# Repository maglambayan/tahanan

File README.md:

# Tahanan Hub

A Home Assistant hub built on the Raspberry Pi Compute Module 5: NVMe storage, Gigabit Ethernet with
802.3bt PoE, USB-C Power Delivery, Wi-Fi and Bluetooth, Zigbee, Thread and Matter, a Z-Wave module
socket, and a microphone, codec and speaker output for voice.

**Revision A is a design package, not a finished product.** The schematic is complete and passes ERC.
The board is placed but not routed, so there are no fabrication files yet. No hardware has been built
and nothing has been validated. Read [docs/status.md](docs/status.md) first.

Since the first commit the open component values and part numbers were checked, the BOM was priced
against DigiKey, and the firmware and Home Assistant OS build files were completed and corrected.
Routing, fabrication files, builds and all testing are still open.

## Layout of this repository

| Path | Contents |
|---|---|
| `docs/` | SoC evaluation, architecture, power and thermal, PCB guide, mechanical, software and recovery, validation plan, status |
| `hardware/` | KiCad 10 project: schematic sheets, board, project library, rules |
| `hardware/gen/` | Generator. `design.py` is the circuit. The KiCad files are built from it |
| `manufacturing/bom/` | Board BOM and system BOM as CSV |
| `mechanical/` | Parametric enclosure script and exported STEP, STL, 3MF |
| `software/` | Bootloader config, `config.txt` block, device tree overlay, Home Assistant OS build recipe |
| `firmware/` | USB-PD controller settings and programming script, radio firmware manifests |

## Building

Needs KiCad 10 and Python 3. From `hardware/`:

```
make sch erc     # schematic, netlist comparison, electrical rule check
make pcb drc     # placed board, design rule check
make docs        # schematic PDF, placement drawing, board STEP, BOM
make fab         # fabrication outputs. Refuses until the board is routed and DRC-clean
```

Enclosure, with CadQuery installed: `python mechanical/enclosure.py`.

The schematic sheets and the board are editable in KiCad. Edits made there are overwritten by the
generator, so either change `design.py` or stop using the generator once manual layout begins.

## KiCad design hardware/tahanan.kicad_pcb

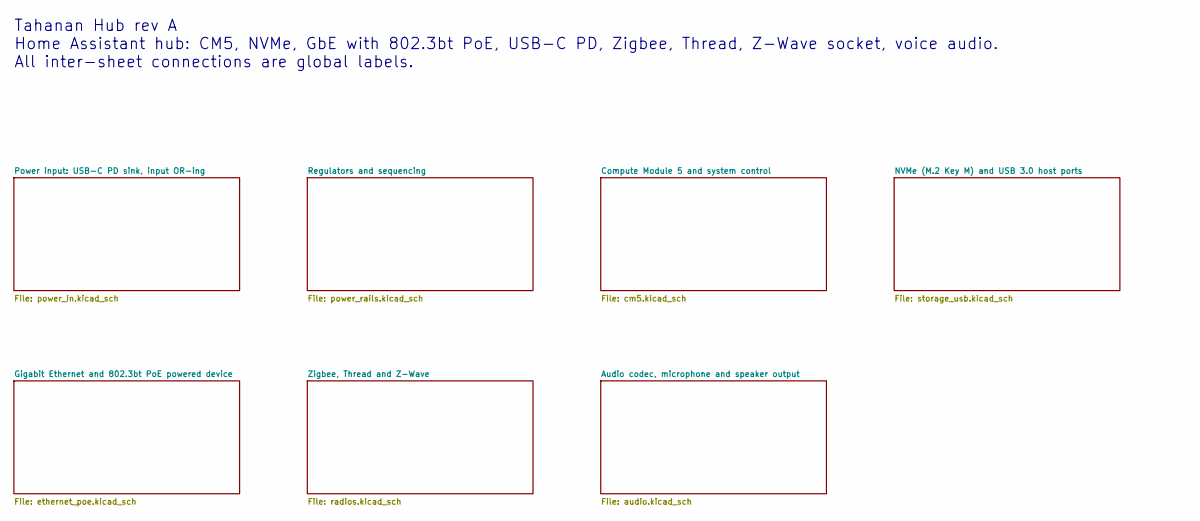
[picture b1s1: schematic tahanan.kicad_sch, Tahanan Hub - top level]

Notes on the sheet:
Tahanan Hub rev A Home Assistant hub: CM5, NVMe, GbE with 802.3bt PoE, USB-C PD, Zigbee, Thread, Z-Wave socket, voice audio. All inter-sheet connections are global labels.

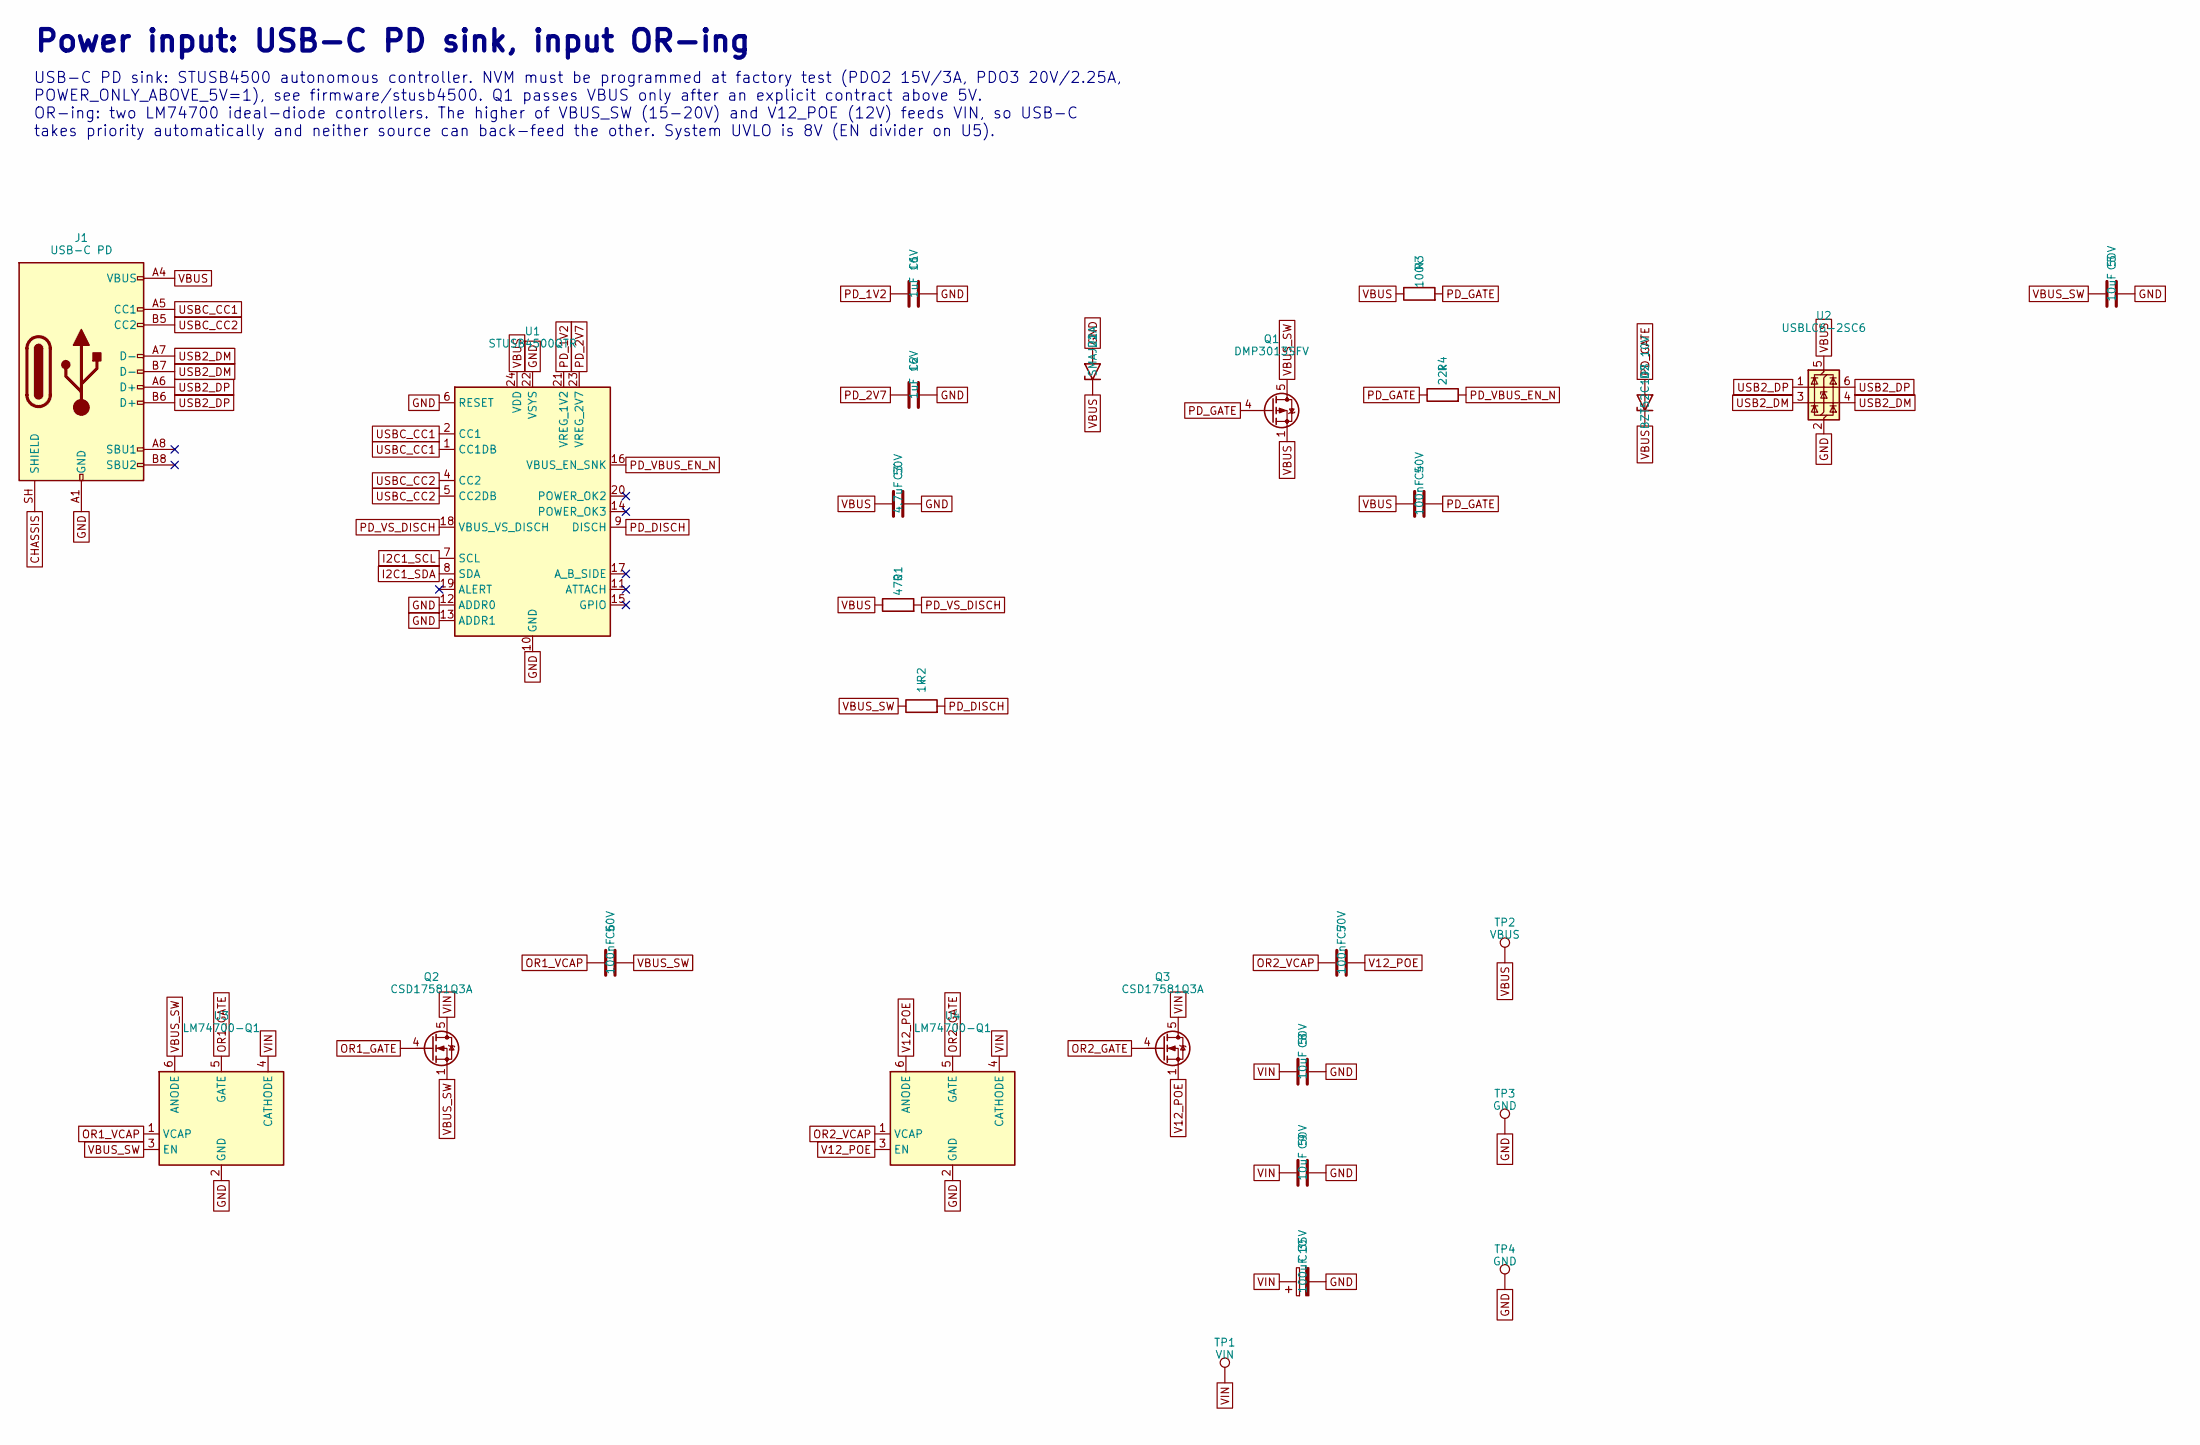
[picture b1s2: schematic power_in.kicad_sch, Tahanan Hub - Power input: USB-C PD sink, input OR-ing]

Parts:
C1, C2: 1uF 16V; C_0402_1005Metric; MPN CL05A105KO5NNNC
C3: 4.7uF 50V; C_0805_2012Metric; MPN CL21A475KBQNNNE
C4, C6, C7: 100nF 50V; C_0603_1608Metric; MPN CL10B104KB8NNNC
C5, C8, C9: 10uF 50V; C_1210_3225Metric; MPN CL32B106KBJNNNE
C10: 100uF 35V; CP_Elec_6.3x7.7; MPN EEE-FT1V101AP
D1: SMAJ22A; D_SMA; MPN SMAJ22A
D2: BZT52C10S 10V; D_SOD-323; MPN BZT52C10S-7-F
J1: USB-C PD; USB_C_Receptacle_GCT_USB4105-xx-A_16P_TopMnt_Horizontal; MPN USB4105-GF-A
Q1: DMP3013SFV; Diodes_PowerDI3333-8; MPN DMP3013SFV-7
Q2, Q3: CSD17581Q3A; VSON-8_3.3x3.3mm_P0.65mm_NexFET; MPN CSD17581Q3A
R1: 470; R_0402_1005Metric; MPN RC0402FR-07470RL
R2: 1k; R_0603_1608Metric; MPN RC0603FR-071kL
R3: 100k; R_0402_1005Metric; MPN RC0402FR-07100kL
R4: 22k; R_0402_1005Metric; MPN RC0402FR-0722kL
TP1: VIN; TestPoint_Pad_D1.5mm
TP2: VBUS; TestPoint_Pad_D1.5mm
TP3, TP4: GND; TestPoint_Pad_D1.5mm
U1: STUSB4500QTR; QFN-24-1EP_4x4mm_P0.5mm_EP2.7x2.7mm; MPN STUSB4500QTR
U2: USBLC6-2SC6; SOT-23-6; MPN USBLC6-2SC6
U3, U4: LM74700-Q1; SOT-23-6; MPN LM74700QDBVRQ1

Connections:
CHASSIS: J1.SH (SHIELD); also elsewhere on the board
GND: C1.2, C2.2, C3.2, C5.2, C8.2, C9.2, C10.2, D1.2 (A2), J1.A1 (GND), J1.A12 (GND), J1.B1 (GND), J1.B12 (GND), TP3.1, TP4.1, U1.6 (RESET), U1.10 (GND), U1.12 (ADDR0), U1.13 (ADDR1), U1.22 (VSYS), U1.25 (GND), U2.2 (GND), U3.2 (GND), U4.2 (GND); also elsewhere on the board
I2C1_SCL: U1.7 (SCL); also elsewhere on the board
I2C1_SDA: U1.8 (SDA); also elsewhere on the board
OR1_GATE: Q2.4 (G), U3.5 (GATE)
OR1_VCAP: C6.1, U3.1 (VCAP)
OR2_GATE: Q3.4 (G), U4.5 (GATE)
OR2_VCAP: C7.1, U4.1 (VCAP)
PD_1V2: C1.1, U1.21 (VREG_1V2)
PD_2V7: C2.1, U1.23 (VREG_2V7)
PD_DISCH: R2.2, U1.9 (DISCH)
PD_GATE: C4.2, D2.2 (A), Q1.4 (G), R3.2, R4.1
PD_VBUS_EN_N: R4.2, U1.16 (VBUS_EN_SNK)
PD_VS_DISCH: R1.2, U1.18 (VBUS_VS_DISCH)
USB2_DM: J1.A7 (D-), J1.B7 (D-), U2.3 (I/O2), U2.4 (I/O2); also elsewhere on the board
USB2_DP: J1.A6 (D+), J1.B6 (D+), U2.1 (I/O1), U2.6 (I/O1); also elsewhere on the board
USBC_CC1: J1.A5 (CC1), U1.1 (CC1DB), U1.2 (CC1)
USBC_CC2: J1.B5 (CC2), U1.4 (CC2), U1.5 (CC2DB)
V12_POE: C7.2, Q3.1 (S), Q3.2 (S), Q3.3 (S), U4.3 (EN), U4.6 (ANODE); also elsewhere on the board
VBUS: C3.1, C4.1, D1.1 (A1), D2.1 (K), J1.A4 (VBUS), J1.A9 (VBUS), J1.B4 (VBUS), J1.B9 (VBUS), Q1.1 (S), Q1.2 (S), Q1.3 (S), R1.1, R3.1, TP2.1, U1.24 (VDD), U2.5 (VBUS)
VBUS_SW: C5.1, C6.2, Q1.5 (D), Q2.1 (S), Q2.2 (S), Q2.3 (S), R2.1, U3.3 (EN), U3.6 (ANODE)
VIN: C8.1, C9.1, C10.1, Q2.5 (D), Q3.5 (D), TP1.1, U3.4 (CATHODE), U4.4 (CATHODE); also elsewhere on the board

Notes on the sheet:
Power input: USB-C PD sink, input OR-ing
USB-C PD sink: STUSB4500 autonomous controller. NVM must be programmed at factory test (PDO2 15V/3A, PDO3 20V/2.25A, POWER_ONLY_ABOVE_5V=1), see firmware/stusb4500. Q1 passes VBUS only after an explicit contract above 5V. OR-ing: two LM74700 ideal-diode controllers. The higher of VBUS_SW (15-20V) a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

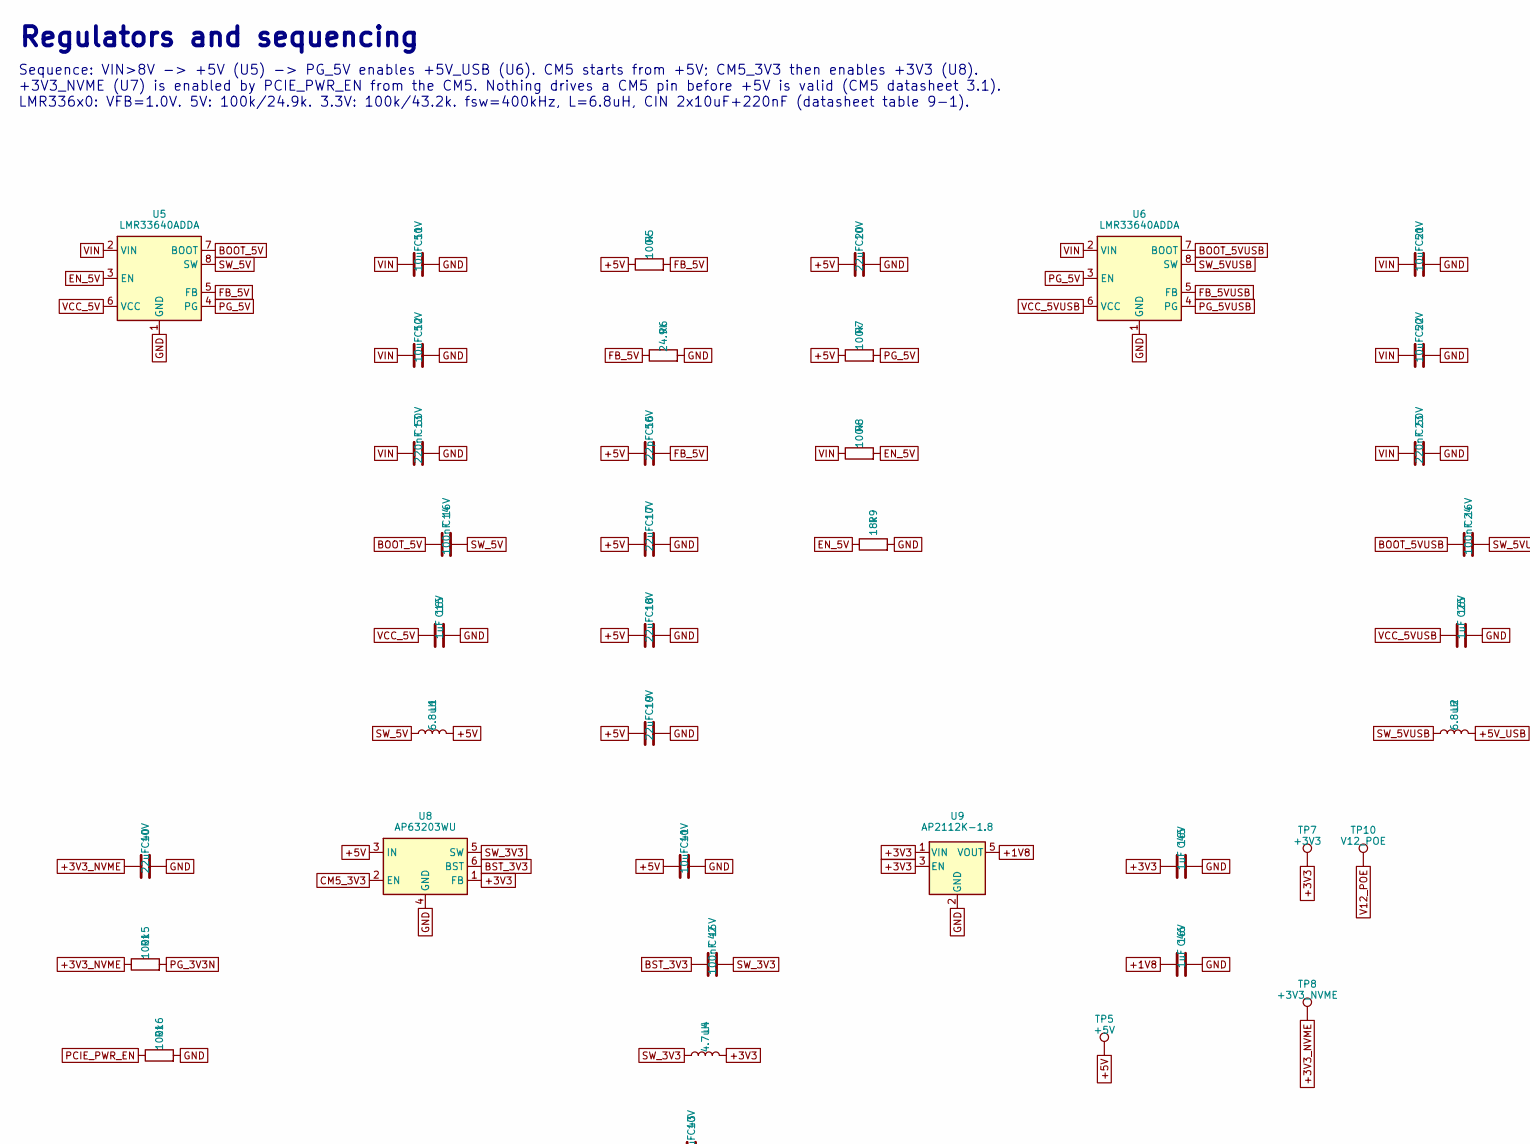
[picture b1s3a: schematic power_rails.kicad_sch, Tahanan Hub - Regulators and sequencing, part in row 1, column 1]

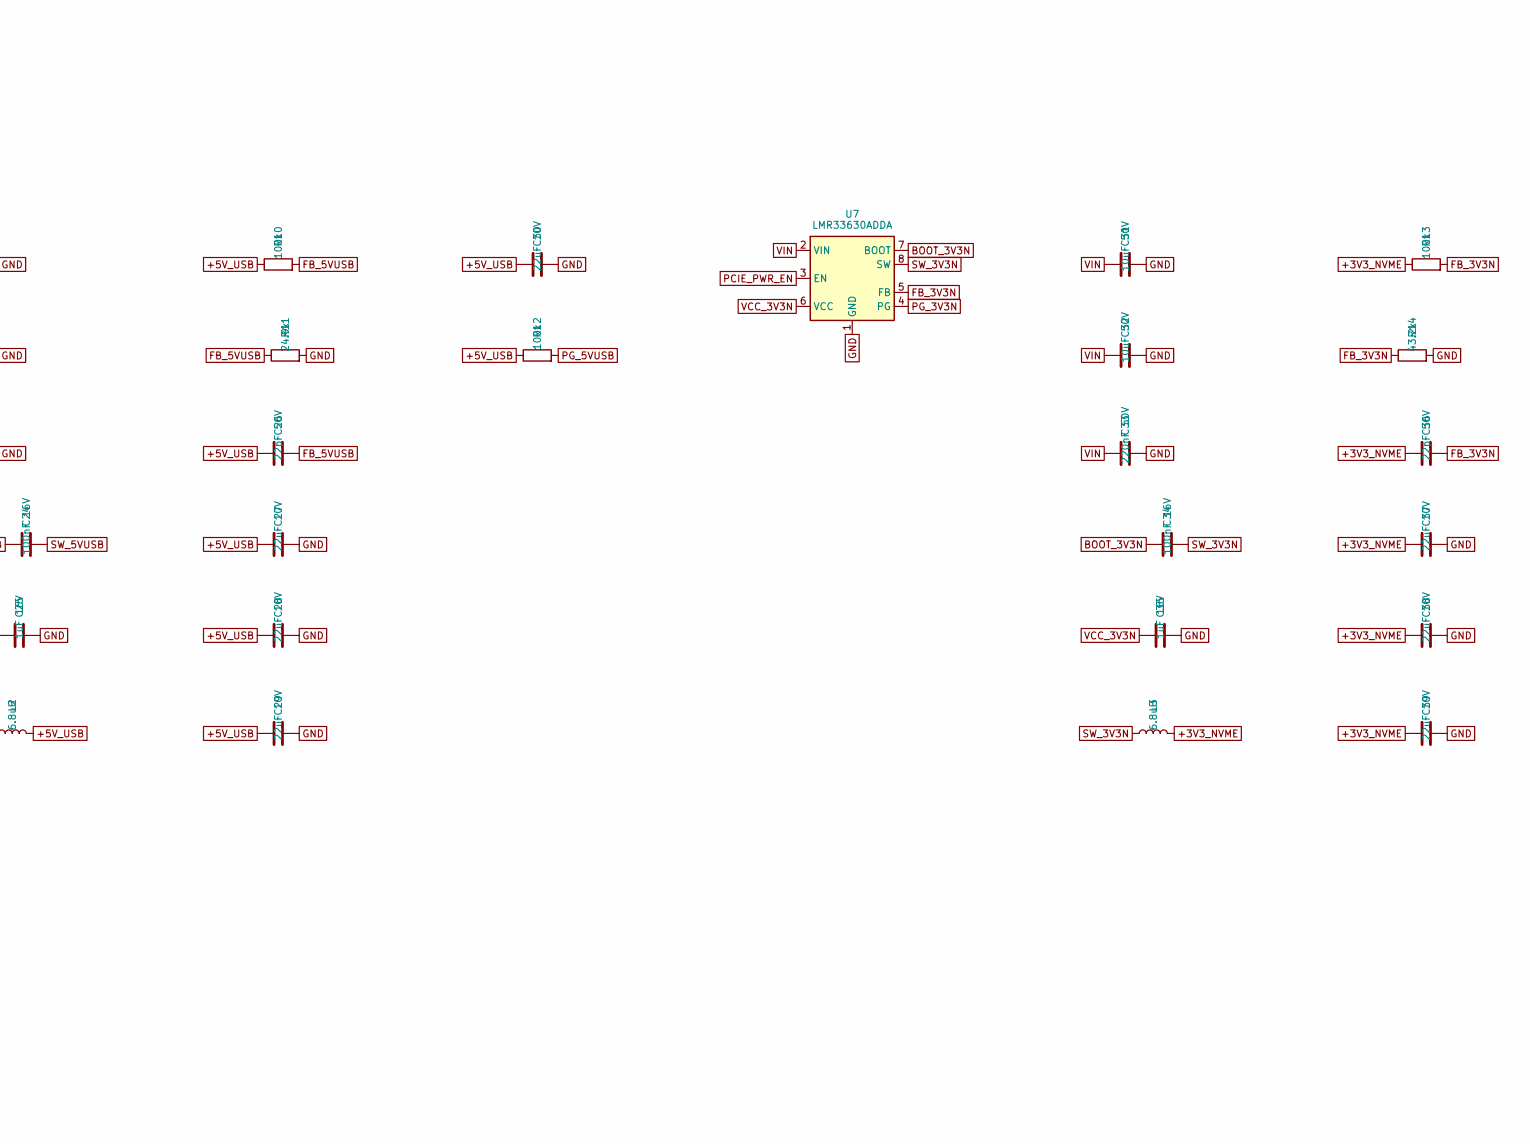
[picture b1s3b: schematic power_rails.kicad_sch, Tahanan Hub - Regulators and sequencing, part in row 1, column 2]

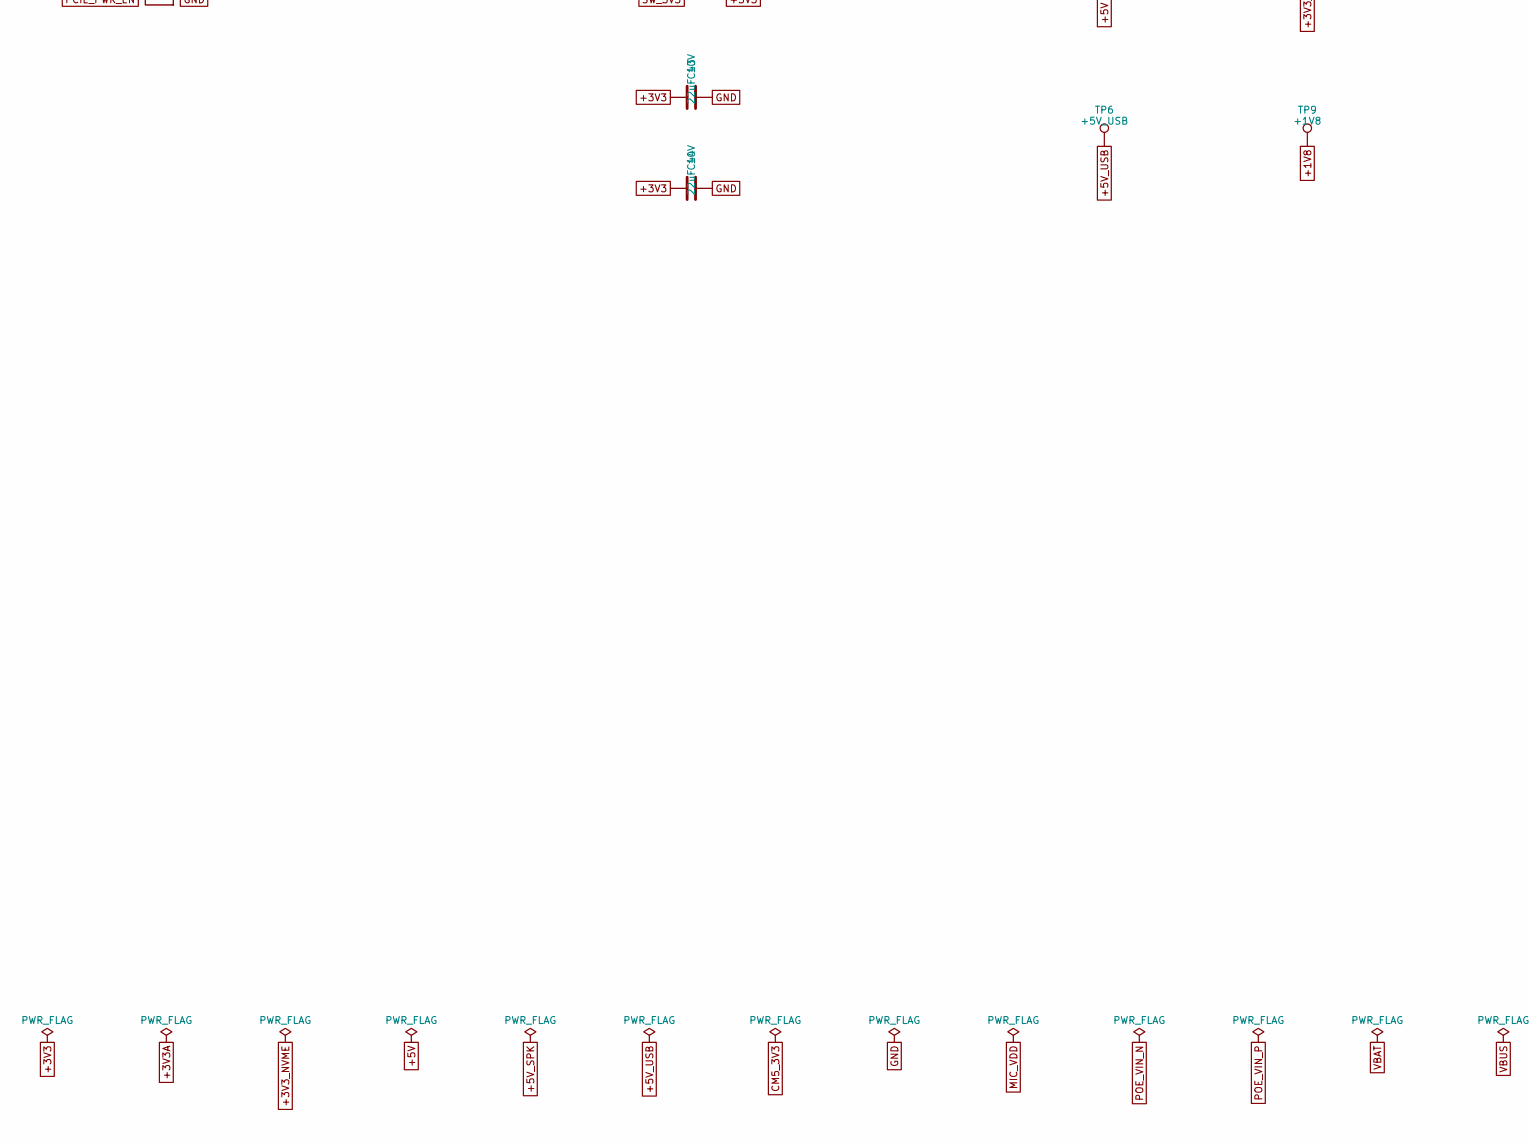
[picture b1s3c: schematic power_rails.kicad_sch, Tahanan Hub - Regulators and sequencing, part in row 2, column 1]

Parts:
C11, C12, C21, C22, C31, C32: 10uF 50V; C_1210_3225Metric; MPN CL32B106KBJNNNE
C13, C23, C33: 220nF 50V; C_0603_1608Metric; MPN CL10B224KB8NNNC
C14, C24, C34, C42: 100nF 16V; C_0402_1005Metric; MPN CL05B104KO5NNNC
C15, C25, C35, C45, C46: 1uF 16V; C_0402_1005Metric; MPN CL05A105KO5NNNC
C16, C26, C36: 22pF 50V; C_0402_1005Metric; MPN CL05C220JB5NNNC
C17, C18, C19, C20, C27, C28, C29, C30, C37, C38, C39, C40, C43, C44: 22uF 10V; C_0805_2012Metric; MPN CL21A226MPQNNNE
C41: 10uF 10V; C_0603_1608Metric; MPN CL10A106KP8NNNC
L1, L2, L3: 6.8uH; L_Bourns_SRP1038C_10.0x10.0mm; MPN SRP1038CC-6R8M
L4: 4.7uH; L_Bourns-SRN4018; MPN SRN4018-4R7M
R5, R7, R8, R10, R12, R13, R15, R16: 100k; R_0402_1005Metric; MPN RC0402FR-07100kL
R6, R11: 24.9k; R_0402_1005Metric; MPN RC0402FR-0724k9L
R9: 18k; R_0402_1005Metric; MPN RC0402FR-0718kL
R14: 43.2k; R_0402_1005Metric; MPN RC0402FR-0743k2L
TP5: +5V; TestPoint_Pad_D1.5mm
TP6: +5V_USB; TestPoint_Pad_D1.5mm
TP7: +3V3; TestPoint_Pad_D1.5mm
TP8: +3V3_NVME; TestPoint_Pad_D1.5mm
TP9: +1V8; TestPoint_Pad_D1.5mm
TP10: V12_POE; TestPoint_Pad_D1.5mm
U5, U6: LMR33640ADDA; Texas_HSOP-8-1EP_3.9x4.9mm_P1.27mm_ThermalVias; MPN LMR33640ADDAR
U7: LMR33630ADDA; Texas_HSOP-8-1EP_3.9x4.9mm_P1.27mm_ThermalVias; MPN LMR33630ADDAR
U8: AP63203WU; TSOT-23-6; MPN AP63203WU-7
U9: AP2112K-1.8; SOT-23-5; MPN AP2112K-1.8TRG1

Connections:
+1V8: C46.1, TP9.1, U9.5 (VOUT); also elsewhere on the board
+3V3: C43.1, C44.1, C45.1, L4.2, TP7.1, U8.1 (FB), U9.1 (VIN), U9.3 (EN); also elsewhere on the board
+3V3_NVME: C36.1, C37.1, C38.1, C39.1, C40.1, L3.2, R13.1, R15.1, TP8.1; also elsewhere on the board
+5V: C16.1, C17.1, C18.1, C19.1, C20.1, C41.1, L1.2, R5.1, R7.1, TP5.1, U8.3 (IN); also elsewhere on the board
+5V_USB: C26.1, C27.1, C28.1, C29.1, C30.1, L2.2, R10.1, R12.1, TP6.1; also elsewhere on the board
BOOT_3V3N: C34.1, U7.7 (BOOT)
BOOT_5V: C14.1, U5.7 (BOOT)
BOOT_5VUSB: C24.1, U6.7 (BOOT)
BST_3V3: C42.1, U8.6 (BST)
CM5_3V3: U8.2 (EN); also elsewhere on the board
EN_5V: R8.2, R9.1, U5.3 (EN)
FB_3V3N: C36.2, R13.2, R14.1, U7.5 (FB)
FB_5V: C16.2, R5.2, R6.1, U5.5 (FB)
FB_5VUSB: C26.2, R10.2, R11.1, U6.5 (FB)
GND: C11.2, C12.2, C13.2, C15.2, C17.2, C18.2, C19.2, C20.2, C21.2, C22.2, C23.2, C25.2, C27.2, C28.2, C29.2, C30.2, C31.2, C32.2, C33.2, C35.2, C37.2, C38.2, C39.2, C40.2, C41.2, C43.2, C44.2, C45.2, C46.2, R6.2, R9.2, R11.2, R14.2, R16.2, U5.1 (GND), U5.9 (GND), U6.1 (GND), U6.9 (GND), U7.1 (GND), U7.9 (GND), U8.4 (GND), U9.2 (GND); also elsewhere on the board
PCIE_PWR_EN: R16.1, U7.3 (EN); also elsewhere on the board
PG_3V3N: R15.2, U7.4 (PG)
PG_5V: R7.2, U5.4 (PG), U6.3 (EN)
PG_5VUSB: R12.2, U6.4 (PG)
SW_3V3: C42.2, L4.1, U8.5 (SW)
SW_3V3N: C34.2, L3.1, U7.8 (SW)
SW_5V: C14.2, L1.1, U5.8 (SW)
SW_5VUSB: C24.2, L2.1, U6.8 (SW)
V12_POE: TP10.1; also elsewhere on the board
VCC_3V3N: C35.1, U7.6 (VCC)
VCC_5V: C15.1, U5.6 (VCC)
VCC_5VUSB: C25.1, U6.6 (VCC)
VIN: C11.1, C12.1, C13.1, C21.1, C22.1, C23.1, C31.1, C32.1, C33.1, R8.1, U5.2 (VIN), U6.2 (VIN), U7.2 (VIN); also elsewhere on the board

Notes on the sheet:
Regulators and sequencing
Sequence: VIN>8V -> +5V (U5) -> PG_5V enables +5V_USB (U6). CM5 starts from +5V; CM5_3V3 then enables +3V3 (U8). +3V3_NVME (U7) is enabled by PCIE_PWR_EN from the CM5. Nothing drives a CM5 pin before +5V is valid (CM5 datasheet 3.1). LMR336x0: VFB=1.0V. 5V: 100k/24.9k. 3.3V: 100k/43.2k. fsw=400kHz,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

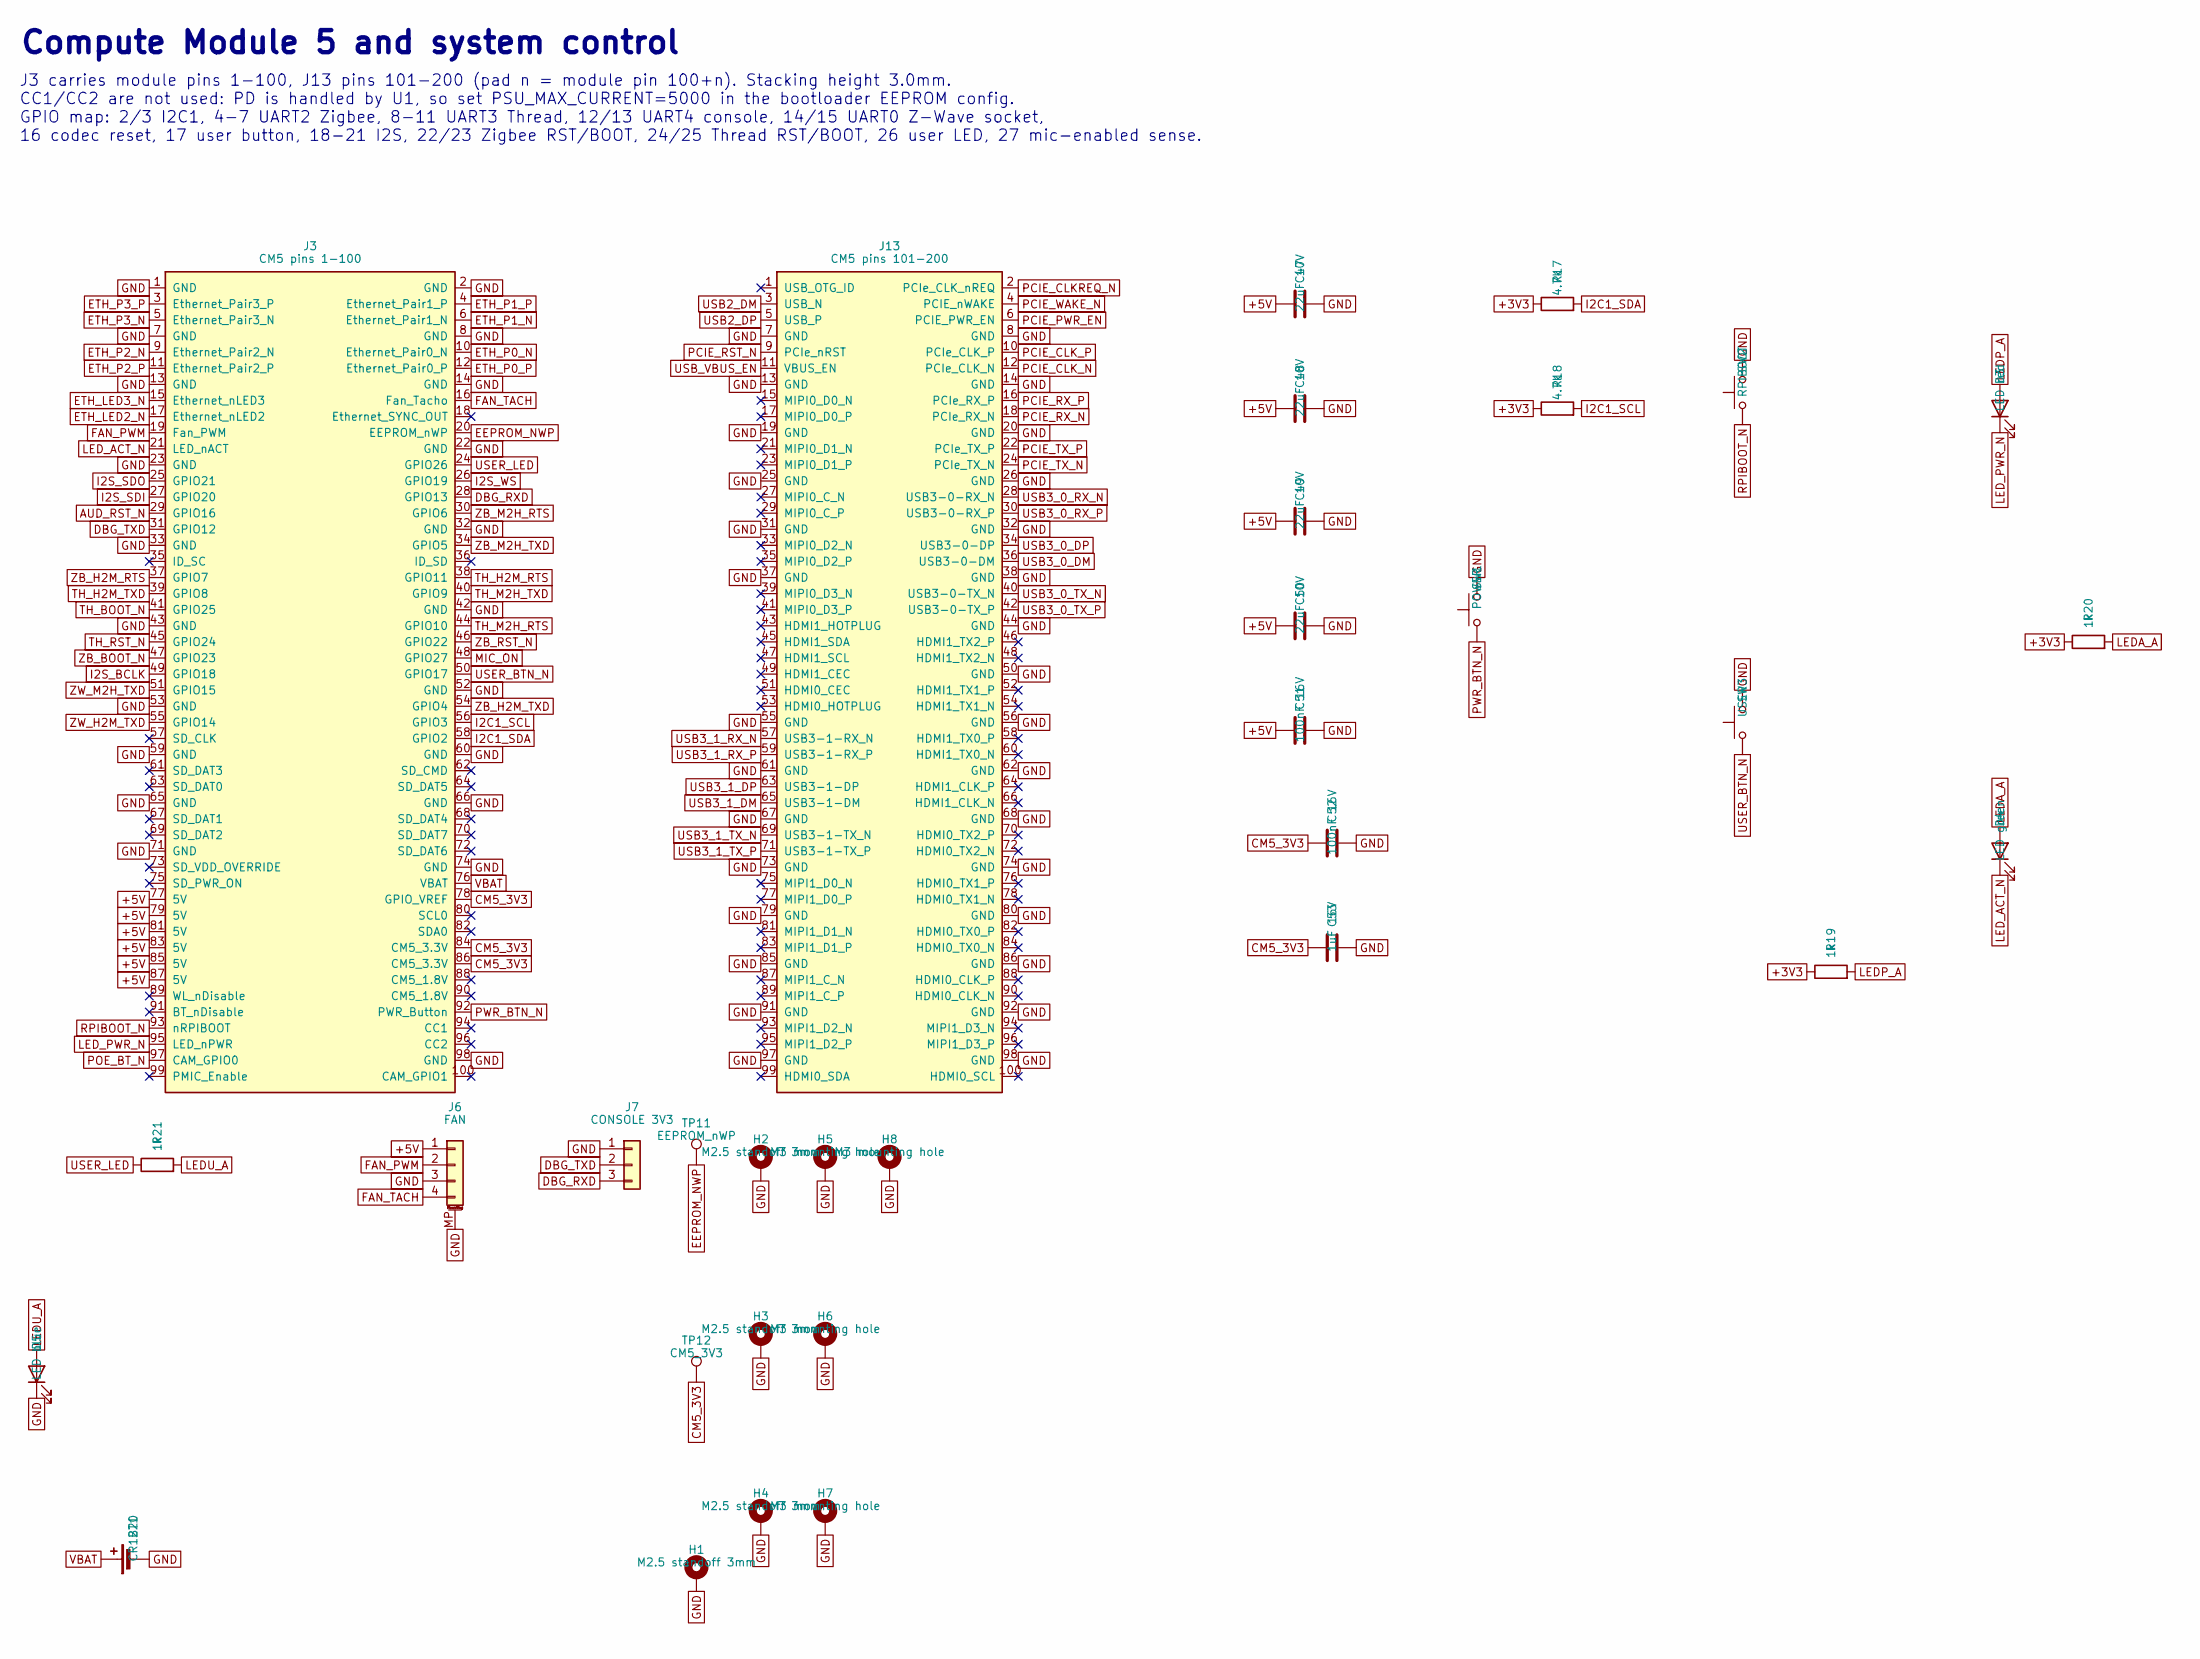
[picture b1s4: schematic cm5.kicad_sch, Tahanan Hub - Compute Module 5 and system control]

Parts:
BT1: CR1220; BatteryHolder_Keystone_3000_1x12mm; MPN 3000
C47, C48, C49, C50: 22uF 10V; C_0805_2012Metric; MPN CL21A226MPQNNNE
C51, C52: 100nF 16V; C_0402_1005Metric; MPN CL05B104KO5NNNC
C53: 1uF 16V; C_0402_1005Metric; MPN CL05A105KO5NNNC
D3: LED red; LED_0603_1608Metric; MPN 150060RS75000
D4: LED green; LED_0603_1608Metric; MPN 150060GS75000
D5: LED blue; LED_0603_1608Metric; MPN 150060BS75000
H1, H2, H3, H4: M2.5 standoff 3mm; Mounting_Wuerth_WA-SMSI-M2.5_H3mm_9774030151; MPN 9774030151R
H5, H6, H7, H8: M3 mounting hole; MountingHole_3.2mm_M3_Pad_Via
J3: CM5 pins 1-100; Hirose_DF40HC(3.0)-100DS-0.4V_2x50_P0.4mm; MPN DF40HC(3.0)-100DS-0.4V(51)
J6: FAN; JST_SH_SM04B-SRSS-TB_1x04-1MP_P1.00mm_Horizontal; MPN SM04B-SRSS-TB
J7: CONSOLE 3V3; PinHeader_1x03_P2.54mm_Vertical; MPN 61300311121
J13: CM5 pins 101-200; Hirose_DF40HC(3.0)-100DS-0.4V_2x50_P0.4mm; MPN DF40HC(3.0)-100DS-0.4V(51)
R17, R18: 4.7k; R_0402_1005Metric; MPN RC0402FR-074k7L
R19, R20, R21: 1k; R_0402_1005Metric; MPN RC0402FR-071kL
SW1: POWER; SW_Tactile_SPST_NO_Straight_CK_PTS636Sx25SMTRLFS; MPN PTS636SM25FSMTRLFS
SW2: RPIBOOT; SW_Tactile_SPST_NO_Straight_CK_PTS636Sx25SMTRLFS; MPN PTS636SM25FSMTRLFS
SW3: USER; SW_Tactile_SPST_NO_Straight_CK_PTS636Sx25SMTRLFS; MPN PTS636SM25FSMTRLFS
TP11: EEPROM_nWP; TestPoint_Pad_D1.5mm
TP12: CM5_3V3; TestPoint_Pad_D1.5mm

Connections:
+3V3: R17.1, R18.1, R19.1, R20.1; also elsewhere on the board
+5V: C47.1, C48.1, C49.1, C50.1, C51.1, J3.77 (5V), J3.79 (5V), J3.81 (5V), J3.83 (5V), J3.85 (5V), J3.87 (5V), J6.1; also elsewhere on the board
AUD_RST_N: J3.29 (GPIO16); also elsewhere on the board
CM5_3V3: C52.1, C53.1, J3.78 (GPIO_VREF), J3.84 (CM5_3.3V), J3.86 (CM5_3.3V), TP12.1; also elsewhere on the board
DBG_RXD: J3.28 (GPIO13), J7.3
DBG_TXD: J3.31 (GPIO12), J7.2
EEPROM_NWP: J3.20 (EEPROM_nWP), TP11.1
ETH_LED2_N: J3.17 (Ethernet_nLED2); also elsewhere on the board
ETH_LED3_N: J3.15 (Ethernet_nLED3); also elsewhere on the board
ETH_P0_N: J3.10 (Ethernet_Pair0_N); also elsewhere on the board
ETH_P0_P: J3.12 (Ethernet_Pair0_P); also elsewhere on the board
ETH_P1_N: J3.6 (Ethernet_Pair1_N); also elsewhere on the board
ETH_P1_P: J3.4 (Ethernet_Pair1_P); also elsewhere on the board
ETH_P2_N: J3.9 (Ethernet_Pair2_N); also elsewhere on the board
ETH_P2_P: J3.11 (Ethernet_Pair2_P); also elsewhere on the board
ETH_P3_N: J3.5 (Ethernet_Pair3_N); also elsewhere on the board
ETH_P3_P: J3.3 (Ethernet_Pair3_P); also elsewhere on the board
FAN_PWM: J3.19 (Fan_PWM), J6.2
FAN_TACH: J3.16 (Fan_Tacho), J6.4
GND: BT1.2 (-), C47.2, C48.2, C49.2, C50.2, C51.2, C52.2, C53.2, D5.1 (K), H1.1, H2.1, H3.1, H4.1, H5.1, H6.1, H7.1, H8.1, J3.1 (GND), J3.2 (GND), J3.7 (GND), J3.8 (GND), J3.13 (GND), J3.14 (GND), J3.22 (GND), J3.23 (GND), J3.32 (GND), J3.33 (GND), J3.42 (GND), J3.43 (GND), J3.52 (GND), J3.53 (GND), J3.59 (GND), J3.60 (GND), J3.65 (GND), J3.66 (GND), J3.71 (GND), J3.74 (GND), J3.98 (GND), J6.3, J6.MP (MountPin), J7.1, J13.7 (GND), J13.8 (GND), J13.13 (GND), J13.14 (GND), J13.19 (GND), J13.20 (GND), J13.25 (GND), J13.26 (GND), J13.31 (GND), J13.32 (GND), J13.37 (GND), J13.38 (GND), J13.44 (GND), J13.50 (GND), J13.55 (GND), J13.56 (GND), J13.61 (GND), J13.62 (GND), J13.67 (GND), J13.68 (GND), J13.73 (GND), J13.74 (GND), J13.79 (GND), J13.80 (GND), J13.85 (GND), J13.86 (GND), J13.91 (GND), J13.92 (GND), J13.97 (GND), J13.98 (GND), SW1.2, SW2.2, SW3.2; also elsewhere on the board
I2C1_SCL: J3.56 (GPIO3), R18.2; also elsewhere on the board
I2C1_SDA: J3.58 (GPIO2), R17.2; also elsewhere on the board
I2S_BCLK: J3.49 (GPIO18); also elsewhere on the board
I2S_SDI: J3.27 (GPIO20); also elsewhere on the board
I2S_SDO: J3.25 (GPIO21); also elsewhere on the board
I2S_WS: J3.26 (GPIO19); also elsewhere on the board
LEDA_A: D4.2 (A), R20.2
LEDP_A: D3.2 (A), R19.2
LEDU_A: D5.2 (A), R21.2
LED_ACT_N: D4.1 (K), J3.21 (LED_nACT)
LED_PWR_N: D3.1 (K), J3.95 (LED_nPWR)
MIC_ON: J3.48 (GPIO27); also elsewhere on the board
PCIE_CLKREQ_N: J13.2 (PCIe_CLK_nREQ); also elsewhere on the board
PCIE_CLK_N: J13.12 (PCIe_CLK_N); also elsewhere on the board
PCIE_CLK_P: J13.10 (PCIe_CLK_P); also elsewhere on the board
PCIE_PWR_EN: J13.6 (PCIE_PWR_EN); also elsewhere on the board
PCIE_RST_N: J13.9 (PCIe_nRST); also elsewhere on the board
PCIE_RX_N: J13.18 (PCIe_RX_N); also elsewhere on the board
PCIE_RX_P: J13.16 (PCIe_RX_P); also elsewhere on the board
PCIE_TX_N: J13.24 (PCIe_TX_N); also elsewhere on the board
PCIE_TX_P: J13.22 (PCIe_TX_P); also elsewhere on the board
PCIE_WAKE_N: J13.4 (PCIE_nWAKE); also elsewhere on the board
POE_BT_N: J3.97 (CAM_GPIO0); also elsewhere on the board
PWR_BTN_N: J3.92 (PWR_Button), SW1.1
RPIBOOT_N: J3.93 (nRPIBOOT), SW2.1
TH_BOOT_N: J3.41 (GPIO25); also elsewhere on the board
TH_H2M_RTS: J3.38 (GPIO11); also elsewhere on the board
TH_H2M_TXD: J3.39 (GPIO8); also elsewhere on the board
TH_M2H_RTS: J3.44 (GPIO10); also elsewhere on the board
TH_M2H_TXD: J3.40 (GPIO9); also elsewhere on the board
TH_RST_N: J3.45 (GPIO24); also elsewhere on the board
USB2_DM: J13.3 (USB_N); also elsewhere on the board
USB2_DP: J13.5 (USB_P); also elsewhere on the board
USB3_0_DM: J13.36 (USB3-0-DM); also elsewhere on the board
USB3_0_DP: J13.34 (USB3-0-DP); also elsewhere on the board
USB3_0_RX_N: J13.28 (USB3-0-RX_N); also elsewhere on the board
USB3_0_RX_P: J13.30 (USB3-0-RX_P); also elsewhere on the board
USB3_0_TX_N: J13.40 (USB3-0-TX_N); also elsewhere on the board
USB3_0_TX_P: J13.42 (USB3-0-TX_P); also elsewhere on the board
USB3_1_DM: J13.65 (USB3-1-DM); also elsewhere on the board
USB3_1_DP: J13.63 (USB3-1-DP); also elsewhere on the board
USB3_1_RX_N: J13.57 (USB3-1-RX_N); also elsewhere on the board
USB3_1_RX_P: J13.59 (USB3-1-RX_P); also elsewhere on the board
USB3_1_TX_N: J13.69 (USB3-1-TX_N); also elsewhere on the board
USB3_1_TX_P: J13.71 (USB3-1-TX_P); also elsewhere on the board
USB_VBUS_EN: J13.11 (VBUS_EN); also elsewhere on the board
USER_BTN_N: J3.50 (GPIO17), SW3.1
USER_LED: J3.24 (GPIO26), R21.1
VBAT: BT1.1 (+), J3.76 (VBAT)
ZB_BOOT_N: J3.47 (GPIO23); also elsewhere on the board
ZB_H2M_RTS: J3.37 (GPIO7); also elsewhere on the board
ZB_H2M_TXD: J3.54 (GPIO4); also elsewhere on the board
ZB_M2H_RTS: J3.30 (GPIO6); also elsewhere on the board
ZB_M2H_TXD: J3.34 (GPIO5); also elsewhere on the board
ZB_RST_N: J3.46 (GPIO22); also elsewhere on the board
ZW_H2M_TXD: J3.55 (GPIO14); also elsewhere on the board
ZW_M2H_TXD: J3.51 (GPIO15); also elsewhere on the board

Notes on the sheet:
Compute Module 5 and system control
J3 carries module pins 1-100, J13 pins 101-200 (pad n = module pin 100+n). Stacking height 3.0mm. CC1/CC2 are not used: PD is handled by U1, so set PSU_MAX_CURRENT=5000 in the bootloader EEPROM config. GPIO map: 2/3 I2C1, 4-7 UART2 Zigbee, 8-11 UART3 Thread, 12/13 UART4 console, 14/15 UART0 Z-Wave 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
